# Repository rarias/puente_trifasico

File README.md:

View this project on [CADLAB.io](https://cadlab.io/project/1865). 

# puente_trifasico
Rectificador trifásico de 10kW
Genera una tensión de continua de 538V/20A

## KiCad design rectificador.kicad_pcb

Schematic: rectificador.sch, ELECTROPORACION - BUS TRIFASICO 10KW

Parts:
C1: 4n7 x 630V; C_Rect_L18.0mm_W6.0mm_P15.00mm_FKS3_FKP3
C2, C3, C4, C5, C6, C7: 0.22uF/400V; C_Rect_L18.0mm_W6.0mm_P15.00mm_FKS3_FKP3
C8: 0.1u X 630V; C_Rect_L24.0mm_W7.0mm_P22.50mm_MKT
C9: NP; C_0603_1608Metric_Pad1.05x0.95mm_HandSolder
C10: 470uF/25V; CP_Radial_D10.0mm_P5.00mm
C11, C13, C14, C17, C18, C20, C21, C22, C30, C32, C33, C34: 0.1uF; C_0603_1608Metric_Pad1.05x0.95mm_HandSolder
C12: 0.1uF; C_0603_1608Metric_Pad1.05x0.95mm_HandSolder; parte Cerámico 0,1uF 16V X7R 0603
C15, C29: 47uFx25V; CP_Radial_D6.3mm_P2.50mm
C16: 470uF/10V; CP_Radial_D10.0mm_P5.00mm
C19: 47uF/25V; CP_Radial_D6.3mm_P2.50mm
C23, C24, C25, C26, C27, C28: 470uFx400V; CP_Radial_D35.0mm_P10.00mm_SnapIn
C31: 47uFx25V/NP; CP_Radial_D6.3mm_P2.50mm
D1, D2, D3, D4, D6, D7, D11, D12, D13, D14: 1N4007; D_DO-35_SOD27_P7.62mm_Horizontal
D5: LED_AZ; LED_0603_1608Metric_Pad1.05x0.95mm_HandSolder; parte Kingbright std led 470nm blue APT1608QBC
D8: LED_VE; LED_0603_1608Metric_Pad1.05x0.95mm_HandSolder; parte SML-LXFP0603SUGCT
D9: LED_RO; LED_0603_1608Metric_Pad1.05x0.95mm_HandSolder; parte SML-LXFP0603SICTR
D10: 2V4/NP; D_DO-35_SOD27_P7.62mm_Horizontal
F1, F2, F3: Fuse; FUSIBLE_CORTO_20MM
F4, F5, F6: 20D431K; RV_Disc_D21.5mm_W5.6mm_P10mm
H1: 6225T; DISIPADOR_6225T_3_ALETAS
J1: TRIF; BORNERA_DT65_B01W_04
J2: CHASIS; terminal_atornillado
J3: PRIM; TerminalBlock_MetzConnect_Type086_RT03402HBLC_1x02_P3.81mm_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
J4: FILTRO_1; BORNERA_DT65_B01W_02
J5: FILTRO_2; BORNERA_DT65_B01W_02
J6: FILTRO_3; BORNERA_DT65_B01W_02
J7: BUS; BORNERA_DT65_B01W_02
J8: COM; BORNERA_DT65_B01W_02
J9: AC_FASE_1; BORNERA_DT65_B01W_02
J10: AC_FASE_2; BORNERA_DT65_B01W_02
J11: AC_FASE_3; BORNERA_DT65_B01W_02
J12: SEC; TerminalBlock_MetzConnect_Type086_RT03402HBLC_1x02_P3.81mm_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
J13: BOB_CONT; TerminalBlock_MetzConnect_Type086_RT03402HBLC_1x02_P3.81mm_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
J14: PUENTE_P; BORNERA_DT65_B01W_04
J15: PUENTE_N; BORNERA_DT65_B01W_04
J16: RES_LIM; BORNERA_DT65_B01W_02
J17: CONTACT; BORNERA_DT65_B01W_02
J18: INDUCT; BORNERA_DT65_B01W_02
J19: MCU; IDC-Header_2x05_P2.54mm_Vertical
J21: VENT; TerminalBlock_MetzConnect_Type086_RT03402HBLC_1x02_P3.81mm_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
J22: TC; TerminalBlock_MetzConnect_Type086_RT03402HBLC_1x02_P3.81mm_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
JP1: MCU/AUTO-NP; PinHeader_1x03_P2.54mm_Vertical
K1: SRD-05VDC-SLC; Relay_SPDT_SANYOU_SRD_Series_Form_C; parte Songle relay SRD-05VDC-SL-C
MH1, MH2, MH3, MH4, MH5, MH6, MH7, MH8, MH9: M3; MountingHole_3.2mm_M3_DIN965_Pad
Q1: 2n2222; TO-92_Inline_Wide
Q2: MMBT3904/NP; SOT-23
R1, R11: 1K; R_0603_1608Metric_Pad1.05x0.95mm_HandSolder
R2: 470/NP; R_0603_1608Metric_Pad1.05x0.95mm_HandSolder
R3: 240; R_0603_1608Metric_Pad1.05x0.95mm_HandSolder
R4, R15, R17: 390; R_0603_1608Metric_Pad1.05x0.95mm_HandSolder
R5: 220; R_0603_1608Metric_Pad1.05x0.95mm_HandSolder; parte Yageo thick film resistor RC0603JR-0722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
R6, R7: 100K; R_0603_1608Metric_Pad1.05x0.95mm_HandSolder
R8, R9, R10, R20: 1M; R_0805_2012Metric_Pad1.15x1.40mm_HandSolder
R12: 1K/NP; R_0603_1608Metric_Pad1.05x0.95mm_HandSolder
R13: 0; R_0603_1608Metric_Pad1.05x0.95mm_HandSolder
R14: 4K7 3W; R_Axial_DIN0414_L11.9mm_D4.5mm_P20.32mm_Horizontal
R16, R18: 10K; R_0603_1608Metric_Pad1.05x0.95mm_HandSolder
R19: NP; R_0603_1608Metric_Pad1.05x0.95mm_HandSolder
SYM1: advertencia_HV; Symbol_HighVoltage_Type2_CopperTop_VerySmall
TP1, TP7: VDD; TestPoint_THTPad_1.8x2.0mm_Drill0.75mm
TP2: 5VDC; TestPoint_THTPad_1.8x2.0mm_Drill0.75mm
TP3: V_BUS; TestPoint_THTPad_1.8x2.0mm_Drill0.75mm
TP4: #V_BUS; TestPoint_THTPad_1.8x2.0mm_Drill0.75mm
TP5: BUS; TestPoint_Loop_D2.54mm_Drill1.5mm_Beaded
TP6, TP9: COM; TestPoint_Loop_D2.54mm_Drill1.5mm_Beaded
TP8, TP15: DGND; TestPoint_THTPad_1.8x2.0mm_Drill0.75mm
TP10: RELE; TestPoint_THTPad_1.8x2.0mm_Drill0.75mm
TP11: FF; TestPoint_THTPad_1.8x2.0mm_Drill0.75mm
TP12: #VCC; TestPoint_THTPad_1.8x2.0mm_Drill0.75mm
TP13: N; TestPoint_Loop_D2.54mm_Drill1.5mm_Beaded
TP14: I_BUS; TestPoint_THTPad_1.8x2.0mm_Drill0.75mm
U1: LM7805_TO220; TO-220-3_Vertical
U2, U3, U9: PC817; DIP-4_W7.62mm
U4: ACS712xLCTR-30A; SOIC-8_3.9x4.9mm_P1.27mm; Parte Allegro ACS712T-ELC-30A
U5: AMC1301; SSO-8_6.8x5.9mm_P1.27mm_Clearance7mm
U6: LM358; SOIC-8_3.9x4.9mm_P1.27mm
U7: MAX6675; SOIC-8_3.9x4.9mm_P1.27mm
U8: 220VAC_5VD_SWITCHING; 220AC_5VDC_SWITCHING

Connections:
/#VCC: C13.1, J19.2, R18.1, TP12.1, U9.3
/#V_BUS: TP4.1, U6.6, U6.7
/AC_1: D1.2, D2.1, J12.2
/AC_2: D3.2, D4.1, J12.1
/BUS_DC: C23.1, C25.1, C27.1, J7.1, J7.2, R20.1, TP5.1, U4.1 (IP+), U4.2 (IP+)
/BUS_POS: J14.1, J14.2, J14.3, J14.4, J16.1, J17.1
/CTRL_CONTACTOR: J19.1, R5.1
/CTRL_RL: JP1.2, Q1.1, R19.1
/FALLA_FASE: C9.1, C12.1, J19.9, R16.1, TP11.1, U2.3
/FASE_1: D13.2, D14.1, F1.2, J1.3
/FASE_2: C8.1, F2.2, J1.2
/FASE_3: F3.2, J1.1, J3.2, J21.1, K1.1, U8.1
/I_BUS: J19.8, TP14.1, U4.7 (VIOUT)
/RELE_A: D6.1, D7.1, K1.5
/RELE_B: D5.1, D6.2, K1.2, Q1.3, Q2.3 (C), TP10.1, U3.4
/TC_CS: J19.5, U7.6
/TC_NEG: J22.2, R13.1, U7.3
/TC_POS: J22.1, U7.2
/TC_SCK: J19.3, U7.5
/TC_SO: J19.7, U7.7
/VCC_5V: C14.1, C15.1, C16.1, C17.1, C22.1, C32.1, D7.2, D9.2, R1.2, R6.1, R12.1, TP2.1, U1.3, U5.1, U8.3, U9.1
/VDD: C18.1, C29.1, C30.1, C33.1, C34.1, D8.2, J19.4, TP1.1, TP7.1, U2.4, U4.8 (VCC), U5.8, U6.8, U7.4, U9.4
/VN_BUS: U5.6, U6.5
/VP_BUS: U5.7, U6.3
/V_BUS: J19.6, TP3.1, U6.1, U6.2
Earth_Protective: C1.2, J2.1
GND: C9.2, C12.2, C13.2, C18.2, C20.2, C29.2, C30.2, C33.2, C34.2, J19.10, R3.2, R13.2, R16.2, R18.2, TP8.1, TP15.1, U3.2, U4.5 (GND), U5.5, U6.4, U7.1
GNDPWR: C10.2, C11.2, C14.2, C15.2, C16.2, C17.2, C19.2, C21.2, C22.2, C24.2, C26.2, C28.2, C31.2, C32.2, D2.2, D4.2, J8.1, J8.2, J15.1, J15.2, J15.3, J15.4, Q1.2, R2.1, R4.2, R7.2, R17.2, R19.2, TP6.1, TP9.1, U1.2, U5.4, U8.5
GNDREF: C1.1, C2.2, C3.2, C4.2, C5.2, C6.2, C7.2, C23.2, C24.1, C25.2, C26.1, C27.2, C28.1, F4.2, F5.2, F6.2, J1.4, J3.1, J13.2, J21.2, TP13.1, U8.2
unnamed: C2.1, F1.1, J4.1
unnamed: C3.1, F2.1, J5.1
unnamed: C4.1, F3.1, J6.1
unnamed: C5.1, F4.1, J4.2, J9.1, J9.2
unnamed: C6.1, F5.1, J5.2, J10.1, J10.2
unnamed: C7.1, F6.1, J6.2, J11.1, J11.2
unnamed: C8.2, R14.1
unnamed: C10.1, C11.1, D1.1, D3.1, U1.1
unnamed: C19.1, C21.1, R6.2, R7.1, R11.2, U5.3
unnamed: C20.1, U4.6 (FILTER)
unnamed: C31.1, D10.1, R12.2
unnamed: D5.2, R1.1
unnamed: D8.1, R3.1
unnamed: D9.1, R4.1
unnamed: D10.2, Q2.1 (B), R2.2
unnamed: D11.1, D13.1, U2.1
unnamed: D11.2, D12.1, R14.2
unnamed: D12.2, D14.2, R15.2
unnamed: J13.1, K1.3
unnamed: J16.2, J17.2, J18.1
unnamed: J18.2, U4.3 (IP-), U4.4 (IP-)
unnamed: JP1.1, U3.3
unnamed: JP1.3, Q2.2 (E)
unnamed: R5.2, U3.1
unnamed: R8.2, R9.1
unnamed: R9.2, R10.1
unnamed: R10.2, R11.1, U5.2
unnamed: R15.1, U2.2
unnamed: R17.1, U9.2
unnamed: R8.1, R20.2

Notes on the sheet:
PCB doble faz 15cm x 18cm
5.5mA
10mA
8mA
foot_err

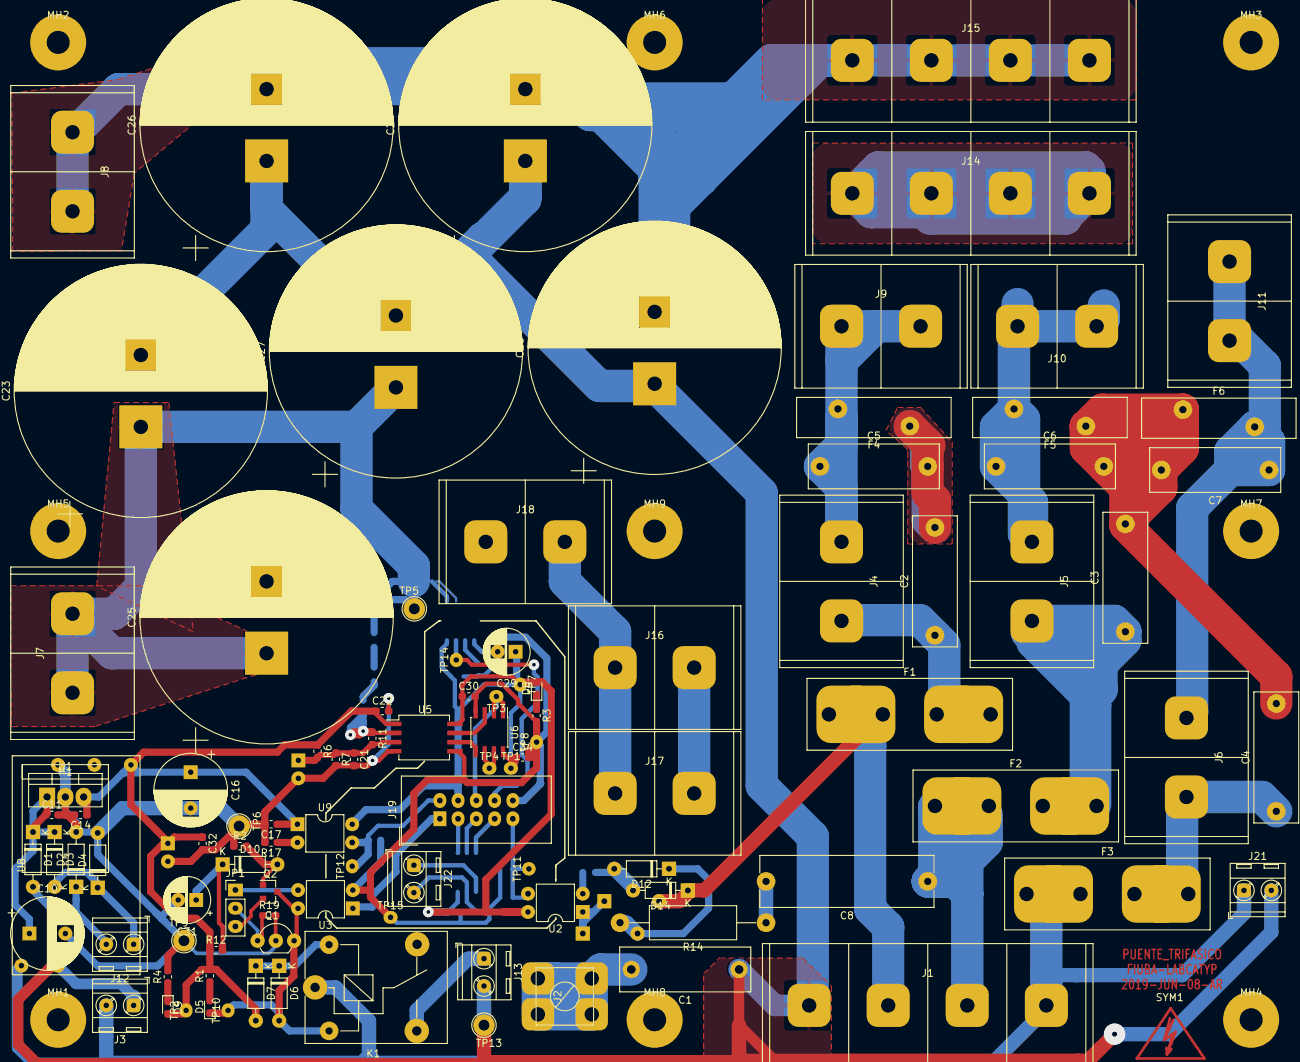
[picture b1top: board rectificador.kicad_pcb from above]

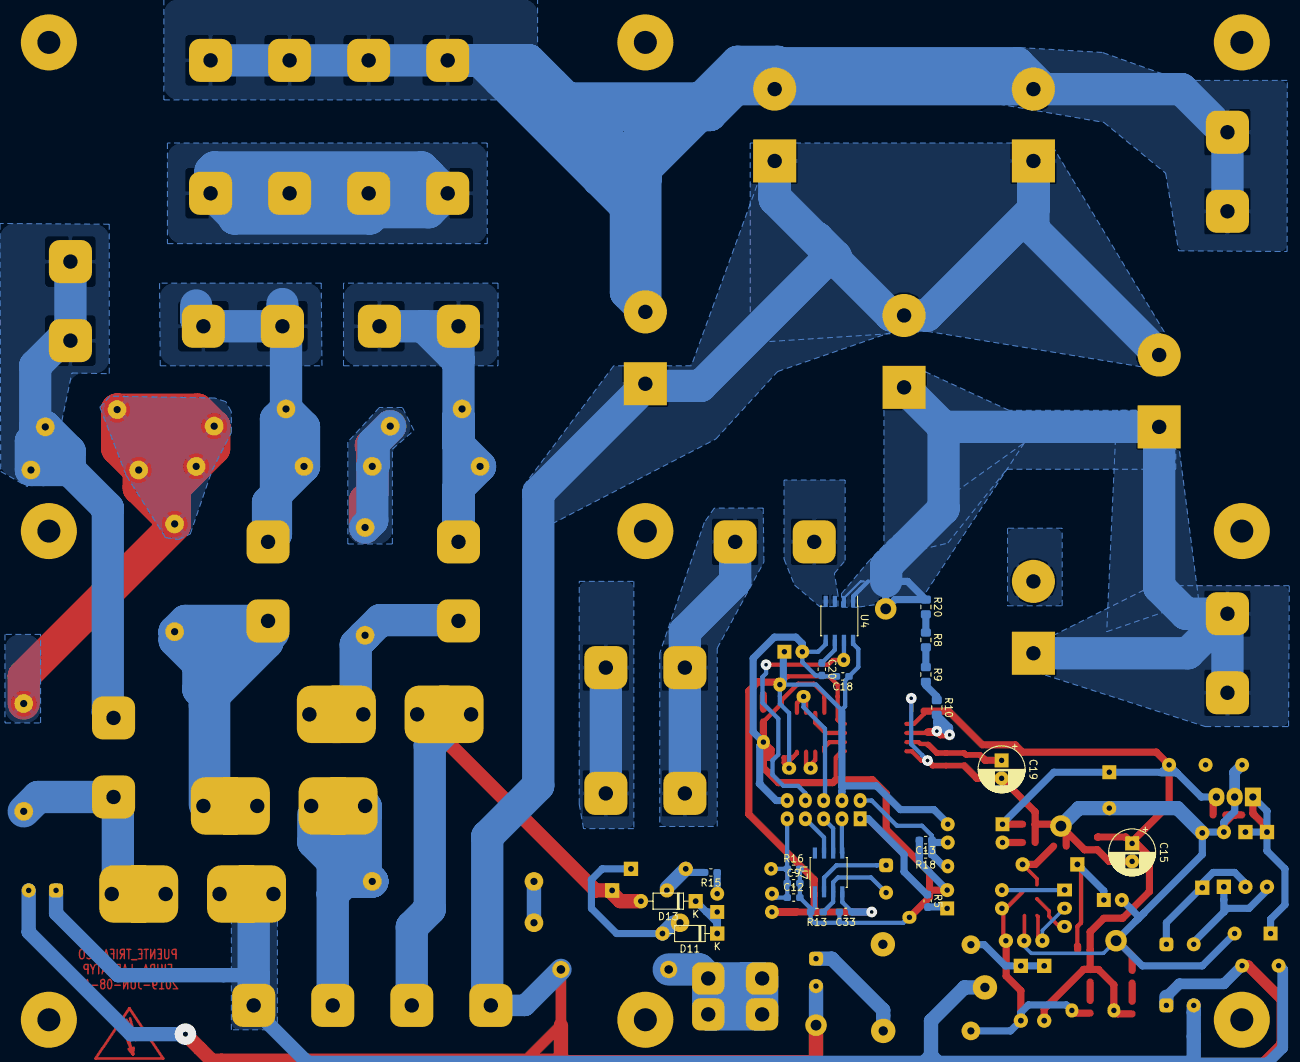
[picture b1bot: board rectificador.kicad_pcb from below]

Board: 4 copper layers, 134 parts (21 on the bottom side), 59 nets.

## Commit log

2019-06-10 agrego esquemático del puente
2019-06-10 agrego pcb
2019-06-10 agrego librerIa
2019-06-10 actualizo readme
2019-06-12 Backlink to CADLAB.io has been added.
2019-06-12 actualizo valores de componentes
2019-06-12 actualizo libreria de símbolos del esquemático
2019-06-12 borro libreria
2019-06-12 recargo librería
